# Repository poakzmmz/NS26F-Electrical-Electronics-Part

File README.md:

<p align="center"><sub>Formula Student Korea 2026 2nd Test Week · NS26F</sub></p>

# NS26F Electrical & Electronics

Formula Student 차량의 **전장 시스템과 임베디드 펌웨어를 직접 설계·통합하고 실제 주행 환경에서 검증한 프로젝트**입니다.

회로/PCB 설계뿐 아니라 STM32 기반 데이터 수집 펌웨어, CAN 통신, ADC/DMA, Timer Input Capture, UART 기반 GNSS·IMU, FATFS Logging, Dashboard/Shift Light까지 차량 내 데이터 흐름 전체를 구현했습니다.

> **Portfolio Focus:** Automotive Embedded Software / Vehicle Electronics / MCU Firmware / System Integration

## Project Overview

| 항목 | 내용 |
|---|---|
| Project | NS26F Formula Student Electrical & Electronics System |
| Role | 전장 파트장 |
| Main Scope | Embedded Firmware, Vehicle CAN, Data Logger, PCB, Harness, System Integration |
| MCU | STM32F405RGT6 |
| Interfaces | CAN, ADC, UART, Timer Input Capture, SDIO |
| Software | C, STM32 HAL, DMA/Interrupt, Ring Buffer/Queue, FATFS |
| Tools | STM32CubeIDE, STM32CubeMX, KiCad |
| Validation | 약 200 km 누적 테스트 주행 및 대회 환경 검증 |

## Problem & Goal

전년도 차량은 각 파트가 설계한 성능을 실제 주행 데이터로 정량적으로 확인하기 어려웠습니다.

이를 개선하기 위해 **CAN, Analog Sensor, Wheel Speed, GNSS/IMU처럼 서로 다른 인터페이스의 데이터를 하나의 MCU에서 수집하고 공통 시간축으로 저장하는 차량용 Data Logger**를 개발했습니다.

단순 Logging 장치가 아니라 실제 차량에서 통신·센서 입력·운전자 표시·데이터 저장이 동시에 수행되는 Embedded System을 목표로 했습니다.

## My Contribution

전장 파트장으로 차량 전장 시스템의 설계·제작·통합 및 검증을 총괄했습니다.

### Embedded Software

- STM32F405 기반 Data Logger Firmware 설계 및 구현
- CAN 500 kbps 수신 인터럽트, Frame Queue 및 차량 Signal 처리
- ADC DMA 기반 Analog Sensor Sampling
- Timer Input Capture 기반 Wheel Speed 측정
- UART 기반 GNSS NMEA Parsing 및 IMU DMA 수신/Packet Parsing
- 공통 Timestamp 기반 CAN / ADC / Wheel / IMU Data Aggregation
- microSD + FATFS 기반 CSV Logging
- Blocking SD I/O에 의한 Data Loss를 줄이기 위한 Queue/Ring Buffer 구조 적용
- SD Write Retry, Fault Logging 및 통신 오류 Recovery 로직 구현
- Nextion Dashboard 및 WS2812B Shift Light 출력
- Firmware 기능별 Module Refactoring 및 Legacy/Test Code 정리

### Hardware & System Integration

- STM32 기반 Data Logger 회로 및 PCB 설계
- 차량 CAN Network 및 Sensor Interface 구성
- 전장 Harness 경로 및 배선 구성
- PCB Bring-up / Debugging / 차량 탑재
- Bench Test 및 반복 실차 주행을 통한 시스템 검증

> 이 저장소에는 전장 파트 팀 산출물도 함께 포함되어 있습니다. 위 항목은 개인 포트폴리오 관점에서 직접 수행하거나 주도한 범위를 별도로 정리한 것입니다.

## Embedded Software Architecture

```mermaid
flowchart LR
    CAN[Vehicle CAN] --> CIRQ[CAN RX / Queue]
    ADC[Analog Sensors] --> ADCDMA[ADC DMA]
    WHEEL[Wheel Speed] --> TIM[Timer Input Capture]
    GNSS[GNSS] --> UART1[UART / Ring Buffer]
    IMU[IMU] --> UART6[UART DMA]

    CIRQ --> AGG[Timestamp / Telemetry Aggregation]
    ADCDMA --> AGG
    TIM --> AGG
    UART1 --> AGG
    UART6 --> AGG

    AGG --> LOG[SD Logger / FATFS]
    AGG --> HMI[Nextion Dashboard]
    AGG --> SHIFT[WS2812B Shift Light]
```

### Runtime Design

실차에서는 통신과 센서 입력이 동시에 발생하고 SD Card Write가 수 ms 이상 Blocking될 수 있습니다.

따라서 ISR에서는 가능한 짧게 데이터를 Queue/Ring Buffer에 적재하고, Parsing·Aggregation·File I/O는 foreground loop에서 처리하도록 구성했습니다.

이 구조를 통해 다음 문제를 다뤘습니다.

- CAN/UART 수신 중 SD Write에 의한 입력 손실
- 서로 다른 Sampling Rate의 Sensor Data 동기화
- UART DMA 및 Interrupt Error Recovery
- SD Card Write/Sync 실패 및 Fault 상태 기록
- HMI 출력과 Logging 작업 간 실행시간 간섭

## Requirements → Implementation

초기 요구사항에는 4-bit SDIO와 USB Mass Storage 기능도 포함되어 있었습니다.

실차 검증 과정에서는 **Logging 안정성을 우선하여 SDIO를 1-bit로 운용하고, FATFS가 SD Card를 사용하는 동안 Host와 동시에 접근할 수 있는 USB MSC 기능은 비활성화**했습니다.

즉 초기 명세를 그대로 유지하기보다 실제 차량 환경에서 발생하는 안정성 문제를 기준으로 설계를 조정했습니다.

초기 요구사항과 실제 구현 중 변경된 설계 판단은 [Software Requirements & Design Decisions](dashboard/datalogger/firmware/REQUIREMENTS.md)에 정리했습니다.

## Firmware Structure

현재 공개 Firmware는 약 4,700줄 규모의 단일 `main.c` 구조에서 기능별 Module로 정리했습니다.

```text
Core/
├── Inc/
│   └── app_internal.h
└── Src/
    ├── main.c
    ├── app.c
    ├── app_state.c
    ├── can_bus.c
    ├── adc_input.c
    ├── wheel_speed.c
    ├── gnss.c
    ├── imu.c
    ├── telemetry.c
    ├── sd_logger.c
    ├── dashboard.c
    ├── shiftlight.c
    ├── app_callbacks.c
    └── led_diag.c
```

각 기능의 책임과 상세 구현은 [Datalogger Firmware](dashboard/datalogger/firmware/README.md)에서 확인할 수 있습니다.

> 실제 차량에서 사용된 통합 Firmware의 동작 경험을 바탕으로 공개 코드 구조를 Module 단위로 정리했습니다. 현재 Refactor Code는 정적 구조 검사를 완료했으며, Hardware Regression은 별도 환경에서 재확인이 필요합니다.

## Hardware & Vehicle Validation

<table>
<tr>
<td width="50%" align="center">
<br>
<sub>STM32 기반 Data Logger PCB — 직접 설계·제작한 V1 보드</sub>
</td>
<td width="50%" align="center">
<br>
<sub>차량 탑재 전/개발 중 전장 Integration Test</sub>
</td>
</tr>
<tr>
<td width="50%" align="center">
<br>
<sub>Dashboard 내부 실제 차량 장착 및 전장 통합</sub>
</td>
<td width="50%" align="center">
<br>
<sub>차량 Harness 제작 및 배선 통합</sub>
</td>
</tr>
</table>

> Integration Test 사진은 개발/검증 단계의 임시 배선을 포함합니다. 최종 양산 배선 품질을 나타내기 위한 사진이 아니라 실제 차량에서 Interface와 기능을 확인한 개발 과정 기록입니다.

## Verification

1. Interface 단위 기능 확인
2. CAN / ADC / Timer / UART 개별 입력 검증
3. SD Logging 및 파일 무결성 확인
4. Dashboard / Shift Light 출력 통합
5. 차량 탑재 후 Sensor / ECU / Harness 통합
6. 반복 주행 중 Data Loss 및 통신 오류 확인
7. 문제 수정 후 재검증

완성된 전장 시스템과 Data Logger는 약 200 km의 누적 테스트 주행과 Formula Student 대회 환경에서 사용했습니다.

> 본 프로젝트의 검증 범위는 Formula Student 차량의 개발 및 대회 환경입니다. 양산 자동차 규격(AEC-Q, ISO 16750 등)에 따른 Automotive Qualification을 의미하지 않습니다.

## Other Electrical Modules

| Module | Description | Path |
|---|---|---|
| Brake Light | LED Brake Light PCB, KiCad 및 생산 파일 | [`brake-light/`](brake-light/) |
| Data Logger | STM32 기반 다채널 차량 Data Acquisition System | [`dashboard/datalogger/`](dashboard/datalogger/) |
| Dashboard UI | Nextion 기반 운전자 표시 UI | [`dashboard/display-ui/`](dashboard/display-ui/) |
| Shift Light | WS2812B 기반 RPM Shift Light | [`dashboard/shiftlight/`](dashboard/shiftlight/) |
| Telemetry | LoRa 기반 차량 데이터 무선 전송 및 Viewer | [`telemetry/`](telemetry/) |
| Harness | 차량 전장 Harness 자료 | [`harness/`](harness/) |

## Repository Structure

```text
NS26F-Electrical-Electronics-Part/
├── brake-light/
├── dashboard/
│   ├── display-ui/
│   ├── datalogger/
│   │   ├── hardware/
│   │   └── firmware/
│   └── shiftlight/
├── telemetry/
├── harness/
└── docs/
```

## Documents

- [Data Logger](dashboard/datalogger/README.md)
- [Data Logger Hardware](dashboard/datalogger/hardware/README.md)
- [Data Logger Firmware](dashboard/datalogger/firmware/README.md)
- [Brake Light](brake-light/README.md)
- [Shift Light](dashboard/shiftlight/README.md)
- [Telemetry](telemetry/README.md)

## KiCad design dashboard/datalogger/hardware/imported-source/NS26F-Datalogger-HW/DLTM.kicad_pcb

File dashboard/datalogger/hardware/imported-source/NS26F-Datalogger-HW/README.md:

# NS26F Datalogger HW

NS26F 데이터로거 KiCad 프로젝트.

## 하드웨어

- MCU: STM32F405RGT6
- 외부 크리스털: 8 MHz
- 3.3 V 레귤레이터: AMS1117-3.3
- CAN 트랜시버: SN65HVD230
- microSD: SDIO 4-bit
- USB Type-C
- SWD
- ADC 입력 6채널
- Input Capture 4채널
- 상태 LED 2채널

## 파일

- `DLTM.kicad_sch`: 회로도
- `DLTM.kicad_pcb`: PCB
- `DLTM.kicad_pro`: 프로젝트 설정
- `DLTM.pdf`: 회로도 PDF
- `production/`: BOM, 실장 좌표, 생산 파일

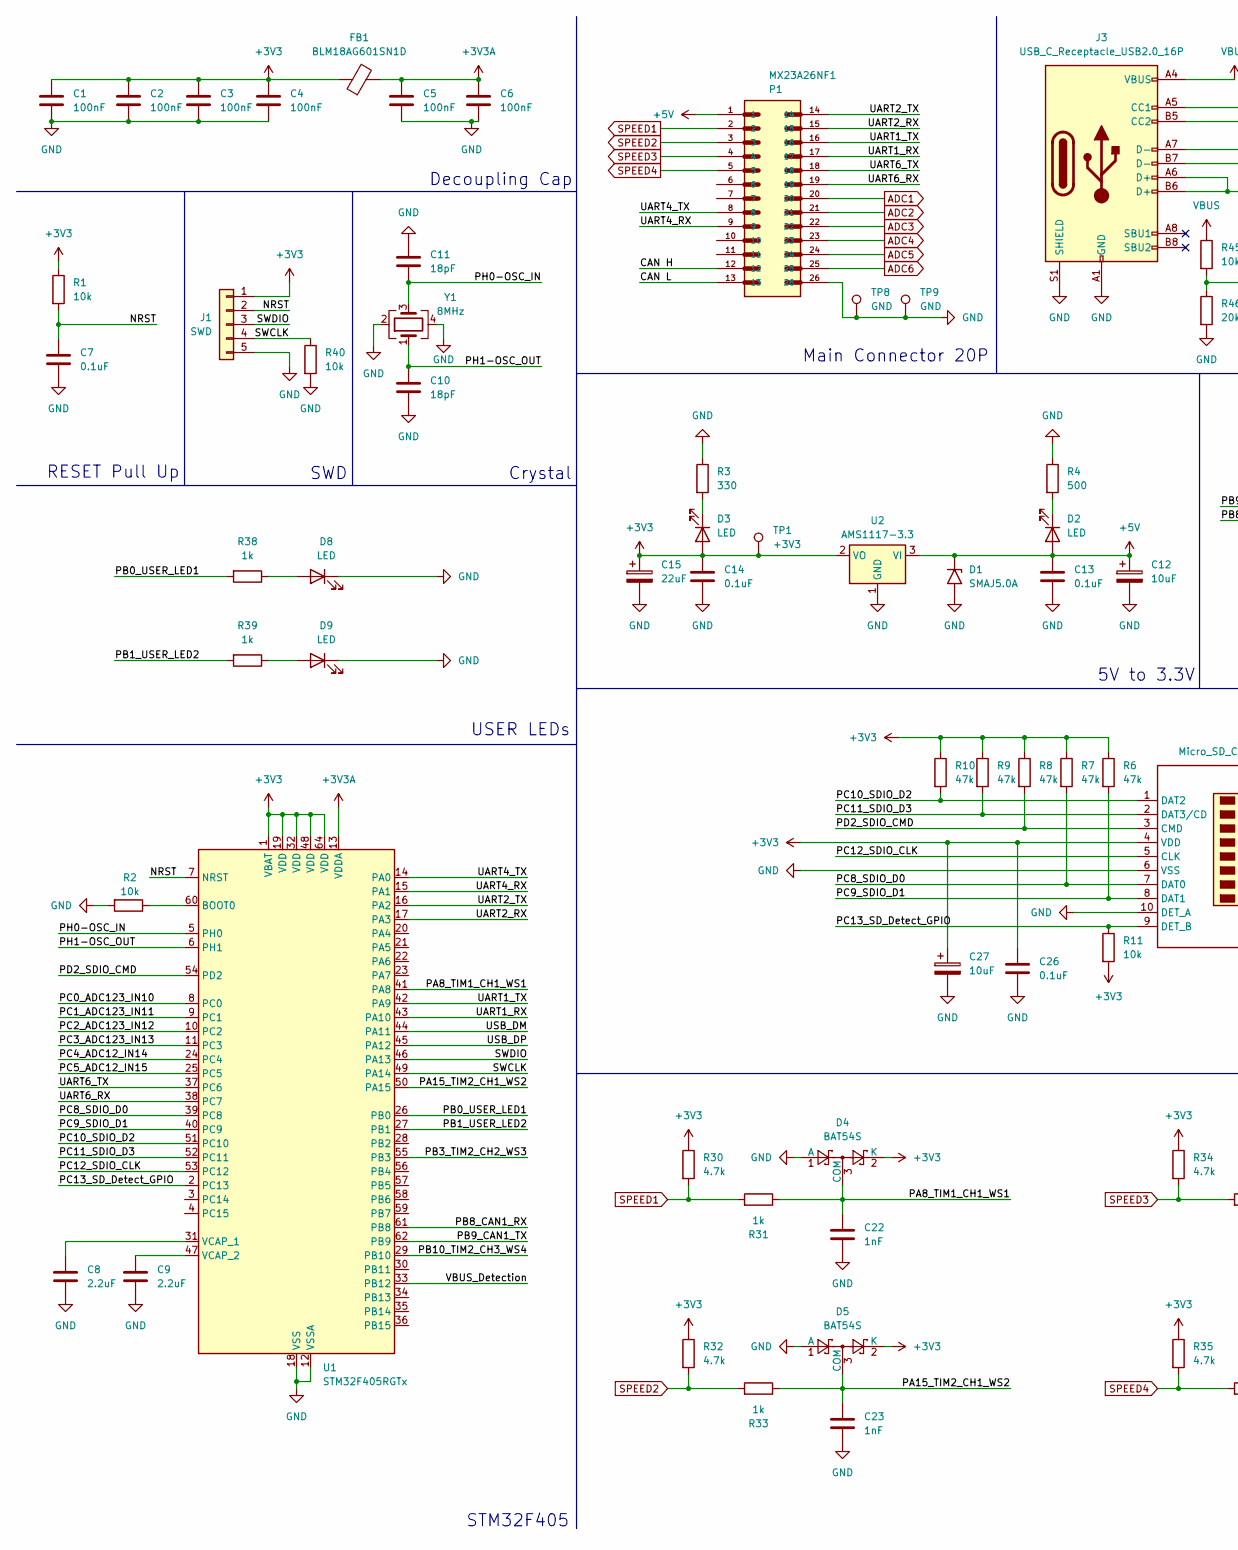
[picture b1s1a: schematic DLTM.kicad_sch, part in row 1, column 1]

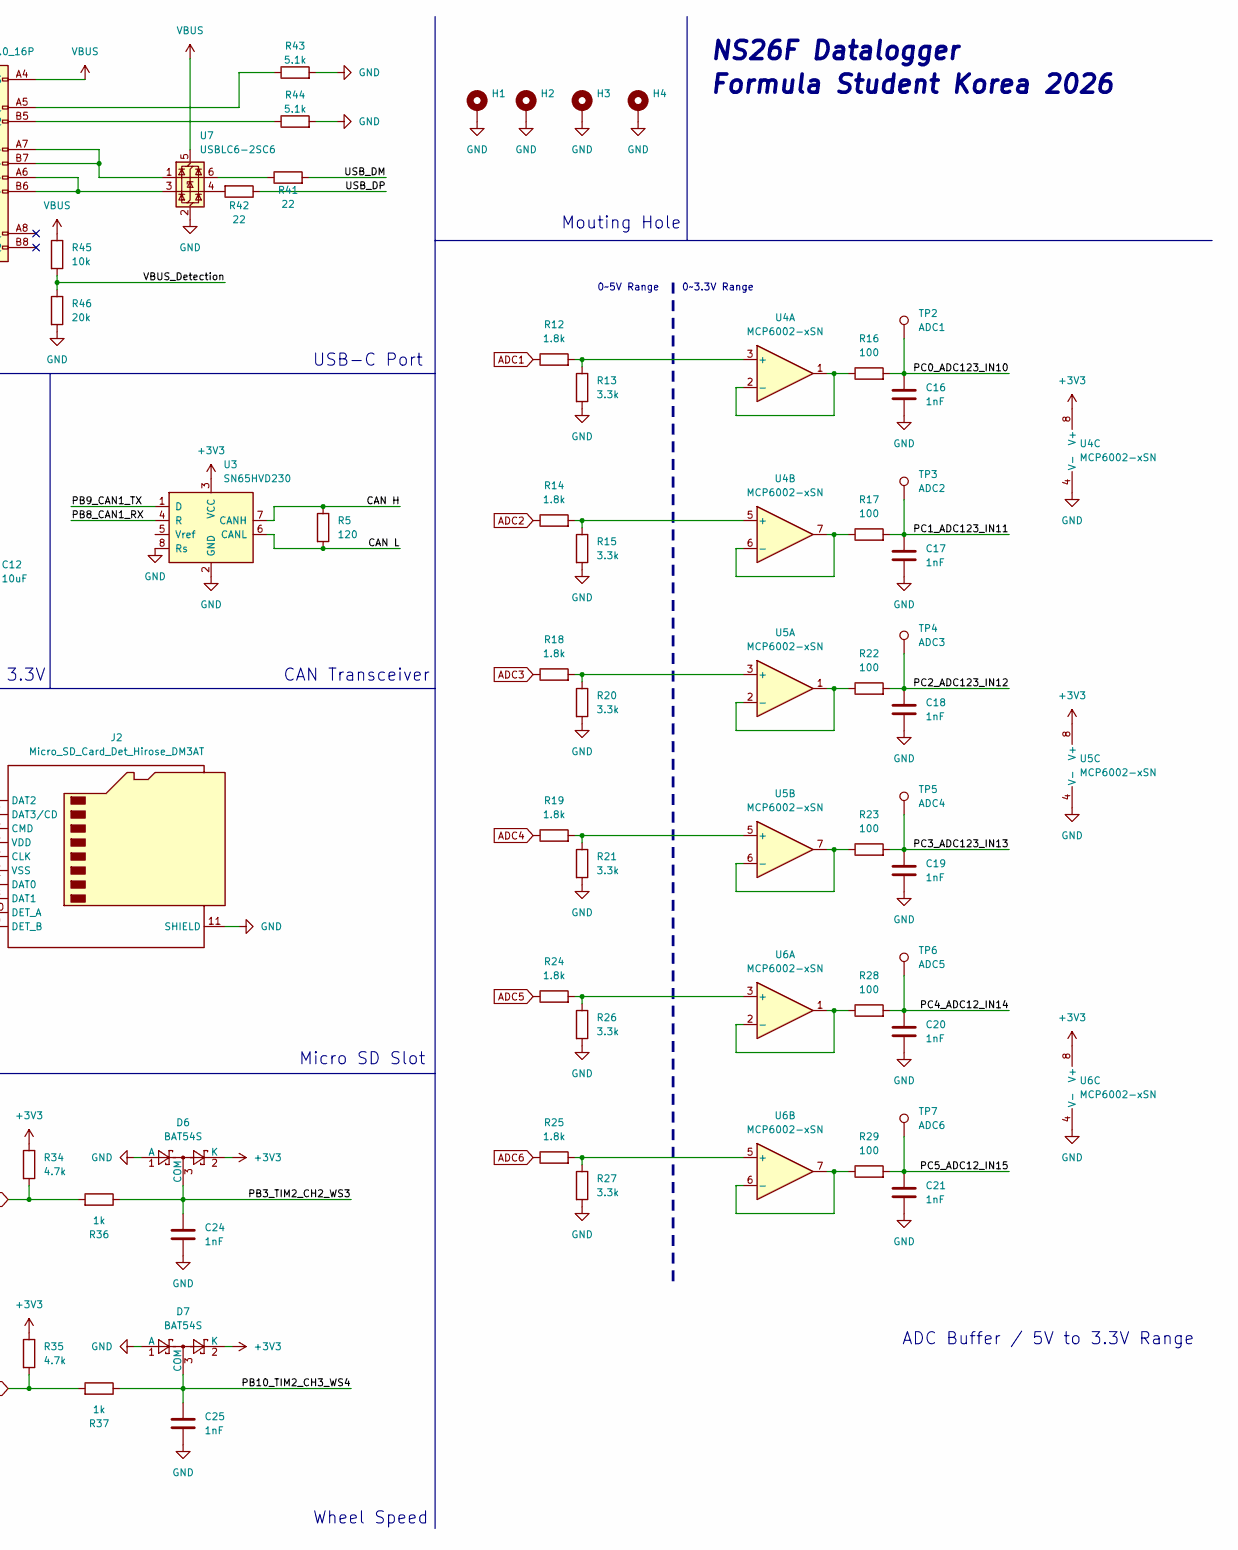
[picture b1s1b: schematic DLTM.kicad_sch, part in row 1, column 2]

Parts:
C1, C2, C3, C4, C5, C6: 100nF; C_0603_1608Metric
C7, C13, C14, C26: 0.1uF; C_0603_1608Metric
C8, C9: 2.2uF; C_0603_1608Metric
C10, C11: 18pF; C_0603_1608Metric
C12, C27: 10uF; CP_Elec_4x5.4
C15: 22uF; CP_Elec_4x5.4
C16, C17, C18, C19, C20, C21, C22, C23, C24, C25: 1nF; C_0603_1608Metric
D1: SMAJ5.0A; D_SMA
D2, D3, D8, D9: LED; LED_0603_1608Metric
D4, D5, D6, D7: BAT54S; SOT-23
FB1: BLM18AG601SN1D; L_0603_1608Metric
H1, H2, H3, H4: MountingHole_Pad; MountingHole_3mm_Pad_TopBottom
J1: SWD; PinHeader_1x05_P2.54mm_Vertical
J2: Micro_SD_Card_Det_Hirose_DM3AT; microSD_HC_Hirose_DM3AT-SF-PEJM5
J3: USB_C_Receptacle_USB2.0_16P; USB_C_Receptacle_HRO_TYPE-C-31-M-12
P1: MX23A26NF1; JAE_MX23A26NF1
R1, R2, R11, R40, R45: 10k; R_0603_1608Metric
R3: 330; R_0603_1608Metric
R4: 500; R_0603_1608Metric
R5: 120; R_0603_1608Metric
R6, R7, R8, R9, R10: 47k; R_0603_1608Metric
R12, R14, R18, R19, R24, R25: 1.8k; R_0603_1608Metric
R13, R15, R20, R21, R26, R27: 3.3k; R_0603_1608Metric
R16, R17, R22, R23, R28, R29: 100; R_0603_1608Metric
R30, R32, R34, R35: 4.7k; R_0603_1608Metric
R31, R33, R36, R37, R38, R39: 1k; R_0603_1608Metric
R41, R42: 22; R_0603_1608Metric
R43, R44: 5.1k; R_0603_1608Metric
R46: 20k; R_0603_1608Metric
TP1: +3V3; TestPoint_Loop_D1.80mm_Drill1.0mm_Beaded
TP2: ADC1; TestPoint_Pad_1.0x1.0mm
TP3: ADC2; TestPoint_Pad_1.0x1.0mm
TP4: ADC3; TestPoint_Pad_1.0x1.0mm
TP5: ADC4; TestPoint_Pad_1.0x1.0mm
TP6: ADC5; TestPoint_Pad_1.0x1.0mm
TP7: ADC6; TestPoint_Pad_1.0x1.0mm
TP8, TP9: GND; TestPoint_Loop_D1.80mm_Drill1.0mm_Beaded
U1: STM32F405RGTx; LQFP-64_10x10mm_P0.5mm
U2: AMS1117-3.3; SOT-223-3_TabPin2
U3: SN65HVD230; SOIC-8_3.9x4.9mm_P1.27mm
U4, U5, U6: MCP6002-xSN; SOIC-8_3.9x4.9mm_P1.27mm
U7: USBLC6-2SC6; SOT-23-6
Y1: 8MHz; Crystal_SMD_3225-4Pin_3.2x2.5mm

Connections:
+3V3: C1.1, C2.1, C3.1, C4.1, C14.1, C15.1, C26.1, C27.1, D3.2 (A), D4.2 (K), D5.2 (K), D6.2 (K), D7.2 (K), FB1.1, J1.1, J2.4 (VDD), R1.1, R6.1, R7.1, R8.1, R9.1, R10.1, R11.2, R30.1, R32.1, R34.1, R35.1, TP1.1, U1.1 (VBAT), U1.19 (VDD), U1.32 (VDD), U1.48 (VDD), U1.64 (VDD), U2.2 (VO), U3.3 (VCC), U4.8 (V+), U5.8 (V+), U6.8 (V+)
+3V3A: C5.1, C6.1, FB1.2, U1.13 (VDDA)
+5V: C12.1, C13.1, D1.1 (A1), D2.2 (A), P1.1, U2.3 (VI)
/CAN H: P1.12, R5.1, U3.7 (CANH)
/CAN L: P1.13, R5.2, U3.6 (CANL)
/NRST: C7.1, J1.2, R1.2, U1.7 (NRST)
/PA8_TIM1_CH1_WS1: C22.1, D4.3 (COM), R31.1, U1.41 (PA8)
/PA15_TIM2_CH1_WS2: C23.1, D5.3 (COM), R33.1, U1.50 (PA15)
/PB0_USER_LED1: R38.2, U1.26 (PB0)
/PB1_USER_LED2: R39.2, U1.27 (PB1)
/PB3_TIM2_CH2_WS3: C24.1, D6.3 (COM), R36.1, U1.55 (PB3)
/PB8_CAN1_RX: U1.61 (PB8), U3.4 (R)
/PB9_CAN1_TX: U1.62 (PB9), U3.1 (D)
/PB10_TIM2_CH3_WS4: C25.1, D7.3 (COM), R37.1, U1.29 (PB10)
/PC0_ADC123_IN10: C16.1, R16.2, TP2.1, U1.8 (PC0)
/PC1_ADC123_IN11: C17.1, R17.2, TP3.1, U1.9 (PC1)
/PC2_ADC123_IN12: C18.1, R22.2, TP4.1, U1.10 (PC2)
/PC3_ADC123_IN13: C19.1, R23.2, TP5.1, U1.11 (PC3)
/PC4_ADC12_IN14: C20.1, R28.2, TP6.1, U1.24 (PC4)
/PC5_ADC12_IN15: C21.1, R29.2, TP7.1, U1.25 (PC5)
/PC8_SDIO_D0: J2.7 (DAT0), R7.2, U1.39 (PC8)
/PC9_SDIO_D1: J2.8 (DAT1), R6.2, U1.40 (PC9)
/PC10_SDIO_D2: J2.1 (DAT2), R10.2, U1.51 (PC10)
/PC11_SDIO_D3: J2.2 (DAT3/CD), R9.2, U1.52 (PC11)
/PC12_SDIO_CLK: J2.5 (CLK), U1.53 (PC12)
/PC13_SD_Detect_GPIO: J2.9 (DET_B), R11.1, U1.2 (PC13)
/PD2_SDIO_CMD: J2.3 (CMD), R8.2, U1.54 (PD2)
/PH0-OSC_IN: C11.2, U1.5 (PH0), Y1.3
/PH1-OSC_OUT: C10.1, U1.6 (PH1), Y1.1
/SWCLK: J1.4, R40.1, U1.49 (PA14)
/SWDIO: J1.3, U1.46 (PA13)
/UART1_RX: P1.17, U1.43 (PA10)
/UART1_TX: P1.16, U1.42 (PA9)
/UART2_RX: P1.15, U1.17 (PA3)
/UART2_TX: P1.14, U1.16 (PA2)
/UART4_RX: P1.9, U1.15 (PA1)
/UART4_TX: P1.8, U1.14 (PA0)
/UART6_RX: P1.19, U1.38 (PC7)
/UART6_TX: P1.18, U1.37 (PC6)
/USB_DM: R41.2, U1.44 (PA11)
/USB_DP: R42.1, U1.45 (PA12)
/VBUS_Detection: R45.2, R46.1, U1.33 (PB12)
ADC1: P1.20, R12.1
ADC2: P1.21, R14.1
ADC3: P1.22, R18.1
ADC4: P1.23, R19.1
ADC5: P1.24, R24.1
ADC6: P1.25, R25.1
GND: C1.2, C2.2, C3.2, C4.2, C5.2, C6.2, C7.2, C8.2, C9.2, C10.2, C11.1, C12.2, C13.2, C14.2, C15.2, C16.2, C17.2, C18.2, C19.2, C20.2, C21.2, C22.2, C23.2, C24.2, C25.2, C26.2, C27.2, D1.2 (A2), D4.1 (A), D5.1 (A), D6.1 (A), D7.1 (A), D8.1 (K), D9.1 (K), H1.1, H2.1, H3.1, H4.1, J1.5, J2.6 (VSS), J2.10 (DET_A), J2.11 (SHIELD), J3.A1 (GND), J3.A12 (GND), J3.B1 (GND), J3.B12 (GND), J3.S1 (SHIELD), P1.26, R2.2, R3.1, R4.1, R13.2, R15.2, R20.2, R21.2, R26.2, R27.2, R40.2, R43.2, R44.2, R46.2, TP8.1, TP9.1, U1.12 (VSSA), U1.18 (VSS), U1.63 (VSS), U2.1 (GND), U3.2 (GND), U3.8 (Rs), U4.4 (V-), U5.4 (V-), U6.4 (V-), U7.2 (GND), Y1.2, Y1.4
unnamed: D2.1 (K), R4.2
unnamed: D3.1 (K), R3.2
unnamed: D8.2 (A), R38.1
unnamed: D9.2 (A), R39.1
unnamed: J3.A5 (CC1), R43.1
unnamed: J3.B5 (CC2), R44.1
unnamed: J3.A6 (D+), J3.B6 (D+), U7.3 (I/O2)
unnamed: J3.A7 (D-), J3.B7 (D-), U7.1 (I/O1)
unnamed: R41.1, U7.6 (I/O1)
unnamed: R42.2, U7.4 (I/O2)
unnamed: R2.1, U1.60 (BOOT0)
unnamed: C8.1, U1.31 (VCAP_1)
unnamed: C9.1, U1.47 (VCAP_2)
unnamed: R12.2, R13.1, U4.3 (+)
unnamed: R16.1, U4.1, U4.2 (-)
unnamed: R14.2, R15.1, U4.5 (+)
unnamed: R17.1, U4.6 (-), U4.7
unnamed: R18.2, R20.1, U5.3 (+)
unnamed: R22.1, U5.1, U5.2 (-)
unnamed: R19.2, R21.1, U5.5 (+)
unnamed: R23.1, U5.6 (-), U5.7
unnamed: R24.2, R26.1, U6.3 (+)
unnamed: R28.1, U6.1, U6.2 (-)
unnamed: R25.2, R27.1, U6.5 (+)
unnamed: R29.1, U6.6 (-), U6.7
SPEED1: P1.2, R30.2, R31.2
SPEED2: P1.3, R32.2, R33.2
SPEED3: P1.4, R34.2, R36.2
SPEED4: P1.5, R35.2, R37.2
VBUS: J3.A4 (VBUS), J3.A9 (VBUS), J3.B4 (VBUS), J3.B9 (VBUS), R45.1, U7.5 (VBUS)

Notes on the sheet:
0~3.3V Range
USB-C Port
Main Connector 20P
STM32F405
Decoupling Cap
USER LEDs
Mouting Hole
NS26F Datalogger
Micro SD Slot
CAN Transceiver
Formula Student Korea 2026
RESET Pull Up
Wheel Speed
5V to 3.3V
ADC Buffer / 5V to 3.3V Range
Crystal
SWD
0~5V Range

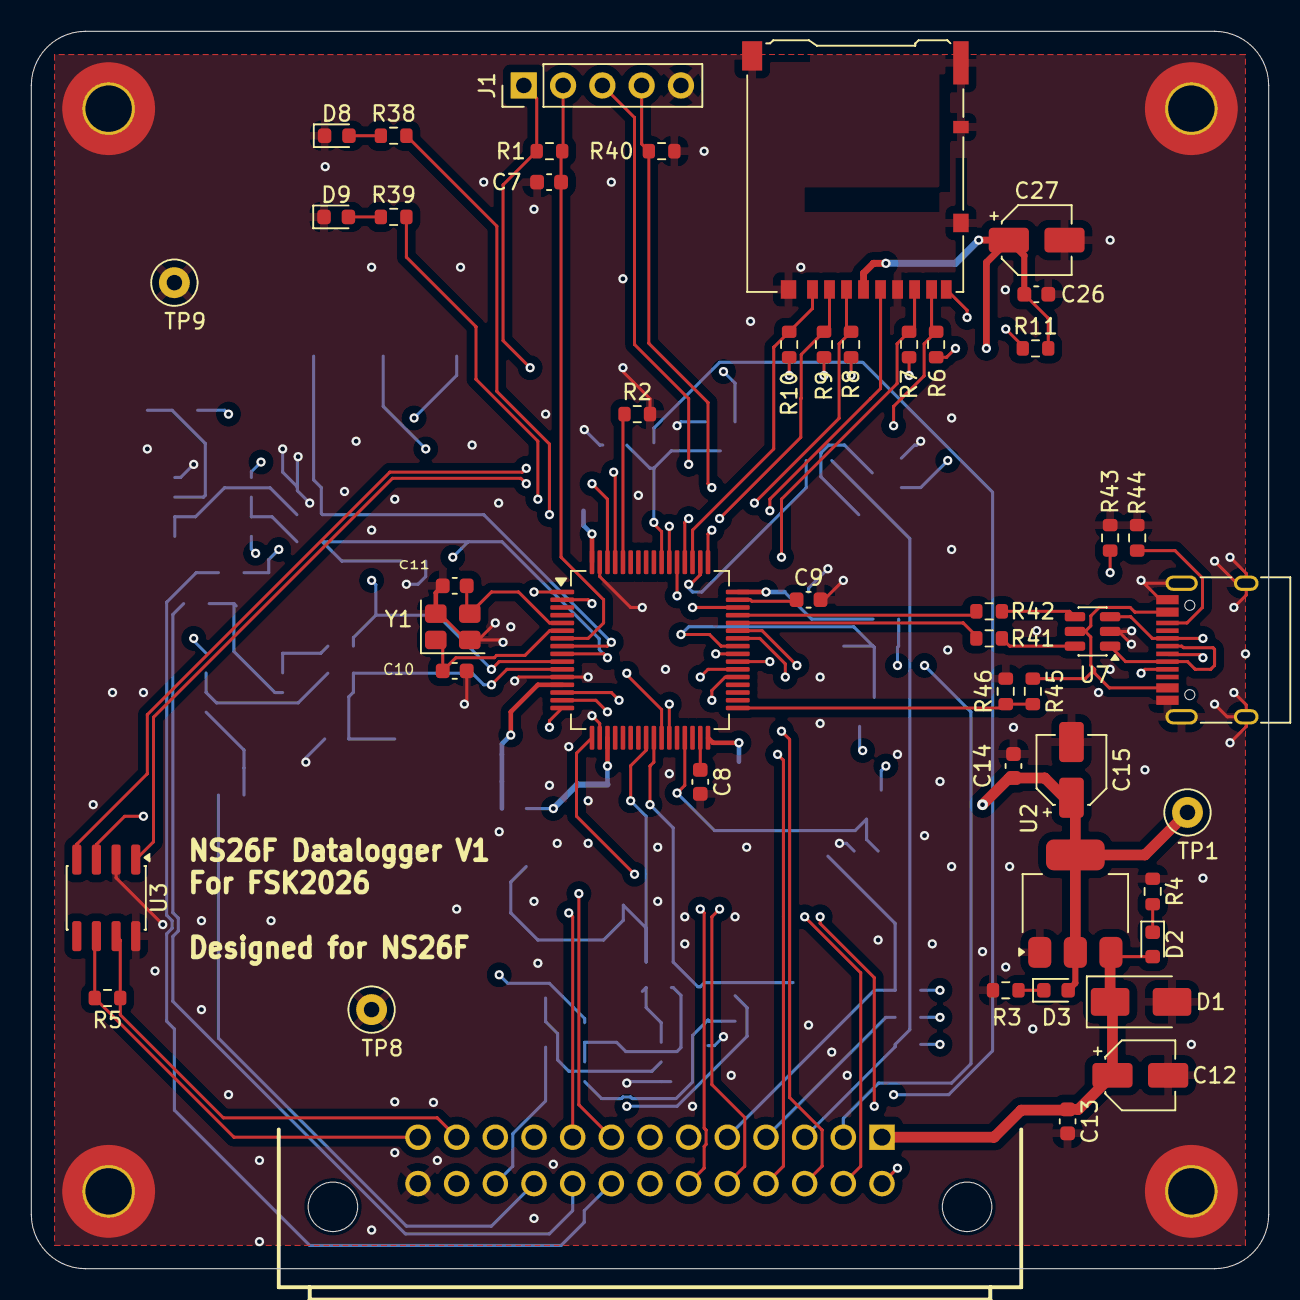
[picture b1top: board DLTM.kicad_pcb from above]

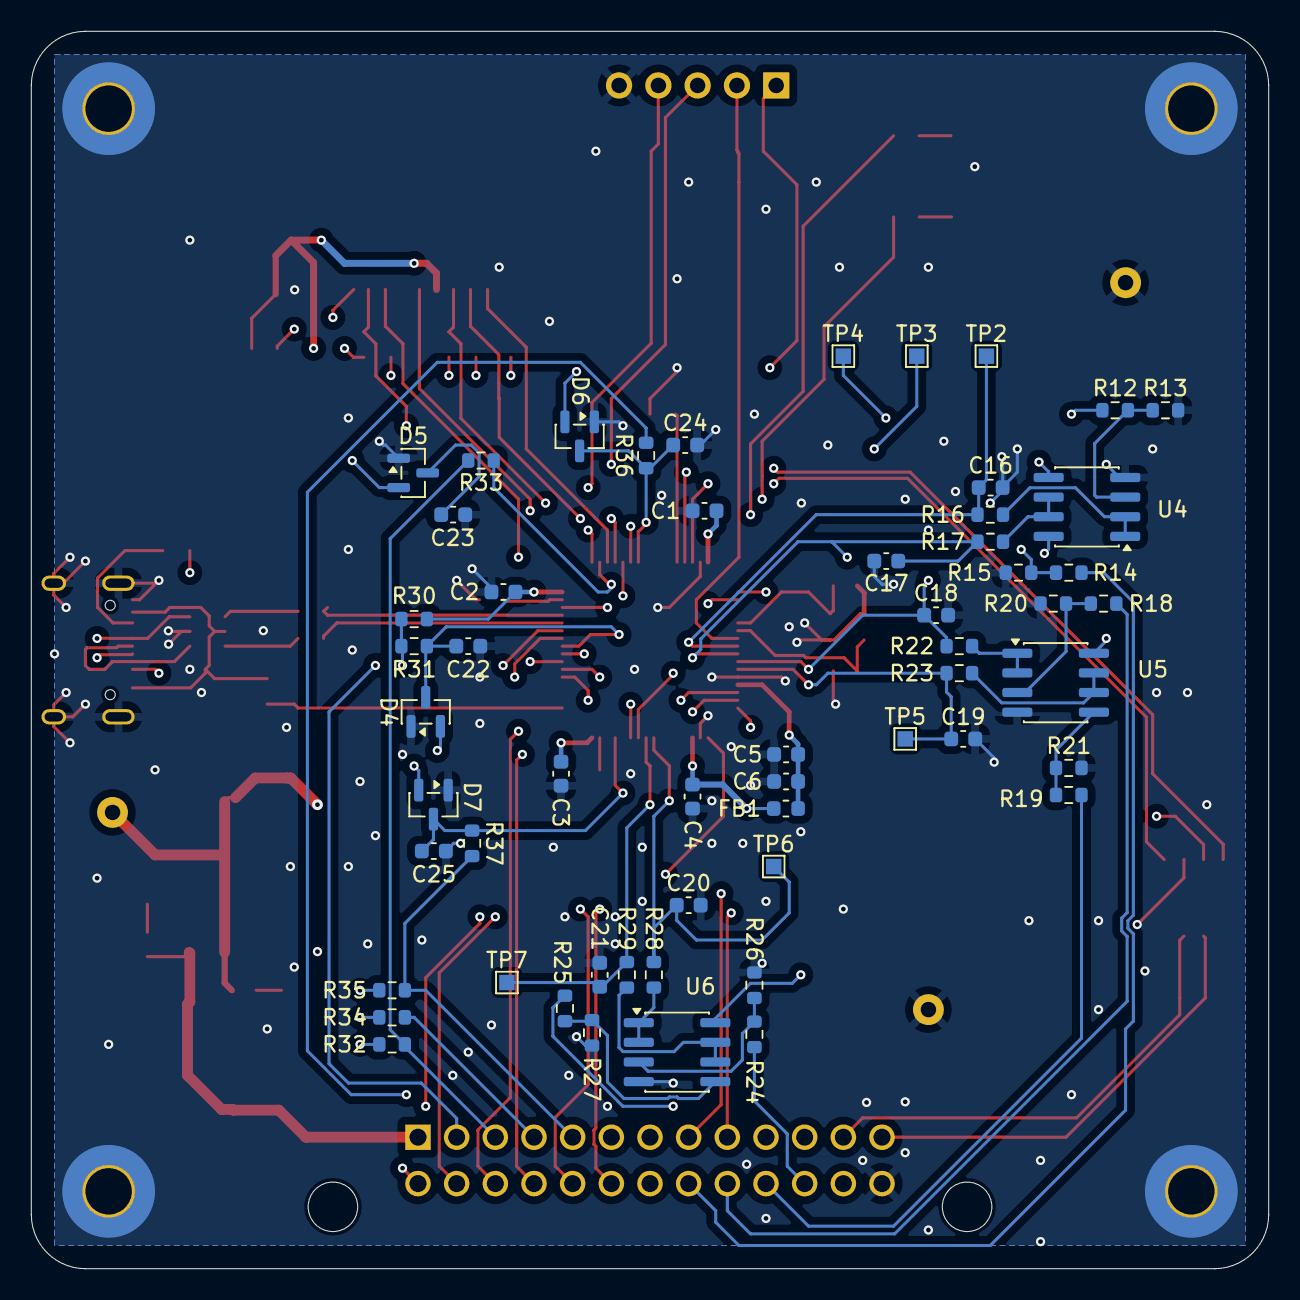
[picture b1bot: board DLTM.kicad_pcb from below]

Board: 4 copper layers, 80.0 x 80.0 mm, 108 parts (56 on the bottom side), 79 nets.

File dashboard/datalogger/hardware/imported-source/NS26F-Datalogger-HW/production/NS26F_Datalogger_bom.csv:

Designator,Footprint,Quantity,Value,LCSC Part #
"C1, C2, C3, C4, C5, C6",0603,6,100nF,
"C10, C11",0603,2,18pF,
"C12, C27",CP_Elec_4x5.4,2,10uF,
"C13, C14, C26, C7",0603,4,0.1uF,
C15,CP_Elec_4x5.4,1,22uF,
"C16, C17, C18, C19, C20, C21, C22, C23, C24, C25",0603,10,1nF,
"C8, C9",0603,2,2.2uF,
D1,D_SMA,1,SMAJ5.0A,
"D2, D3, D8, D9",0603,4,LED,
"D4, D5, D6, D7",SOT-23,4,BAT54S,
FB1,0603,1,BLM18AG601SN1D,
J1,PinHeader_1x05_P2.54mm_Vertical,1,SWD,
J2,microSD_HC_Hirose_DM3AT-SF-PEJM5,1,Micro_SD_Card_Det_Hirose_DM3AT,
J3,USB_C_Receptacle_HRO_TYPE-C-31-M-12,1,USB_C_Receptacle_USB2.0_16P,
P1,JAE_MX23A26NF1,1,MX23A26NF1,
"R1, R11, R2, R40, R45",0603,5,10k,
"R10, R6, R7, R8, R9",0603,5,47k,
"R12, R14, R18, R19, R24, R25",0603,6,1.8k,
"R13, R15, R20, R21, R26, R27",0603,6,3.3k,
"R16, R17, R22, R23, R28, R29",0603,6,100,
R3,0603,1,330,
"R30, R32, R34, R35",0603,4,4.7k,
"R31, R33, R36, R37, R38, R39",0603,6,1k,
R4,0603,1,500,
"R41, R42",0603,2,22,
"R43, R44",0603,2,5.1k,
R46,0603,1,20k,
R5,0603,1,120,
TP1,TestPoint_Loop_D1.80mm_Drill1.0mm_Beaded,1,+3V3,
TP2,TestPoint_Pad_1.0x1.0mm,1,ADC1,
TP3,TestPoint_Pad_1.0x1.0mm,1,ADC2,
TP4,TestPoint_Pad_1.0x1.0mm,1,ADC3,
TP5,TestPoint_Pad_1.0x1.0mm,1,ADC4,
TP6,TestPoint_Pad_1.0x1.0mm,1,ADC5,
TP7,TestPoint_Pad_1.0x1.0mm,1,ADC6,
"TP8, TP9",TestPoint_Loop_D1.80mm_Drill1.0mm_Beaded,2,GND,
U1,LQFP-64_10x10mm_P0.5mm,1,STM32F405RGTx,
U2,SOT-223-3_TabPin2,1,AMS1117-3.3,
U3,SOIC-8_3.9x4.9mm_P1.27mm,1,SN65HVD230,
"U4, U5, U6",SOIC-8_3.9x4.9mm_P1.27mm,3,MCP6002-xSN,
U7,SOT-23-6,1,USBLC6-2SC6,
Y1,Crystal_SMD_3225-4Pin_3.2x2.5mm,1,8MHz,

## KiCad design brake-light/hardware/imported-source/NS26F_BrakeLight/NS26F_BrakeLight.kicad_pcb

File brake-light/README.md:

# NS26F Brake Light

NS26F 브레이크등 KiCad 프로젝트.

## 구성

- 0805 LED 68개
- 330 Ω 1206 저항 17개
- TVS 다이오드 1개
- SS34 다이오드 1개

## 파일

- `hardware/imported-source/NS26F_BrakeLight/NS26F_BrakeLight.kicad_sch`: 회로도
- `hardware/imported-source/NS26F_BrakeLight/NS26F_BrakeLight.kicad_pcb`: PCB
- `hardware/imported-source/NS26F_BrakeLight/production/`: BOM, 실장 좌표, 생산 ZIP

`production/`에는 초기 버전과 V2 파일이 함께 있다. 두 버전의 BOM 내용은 같다.

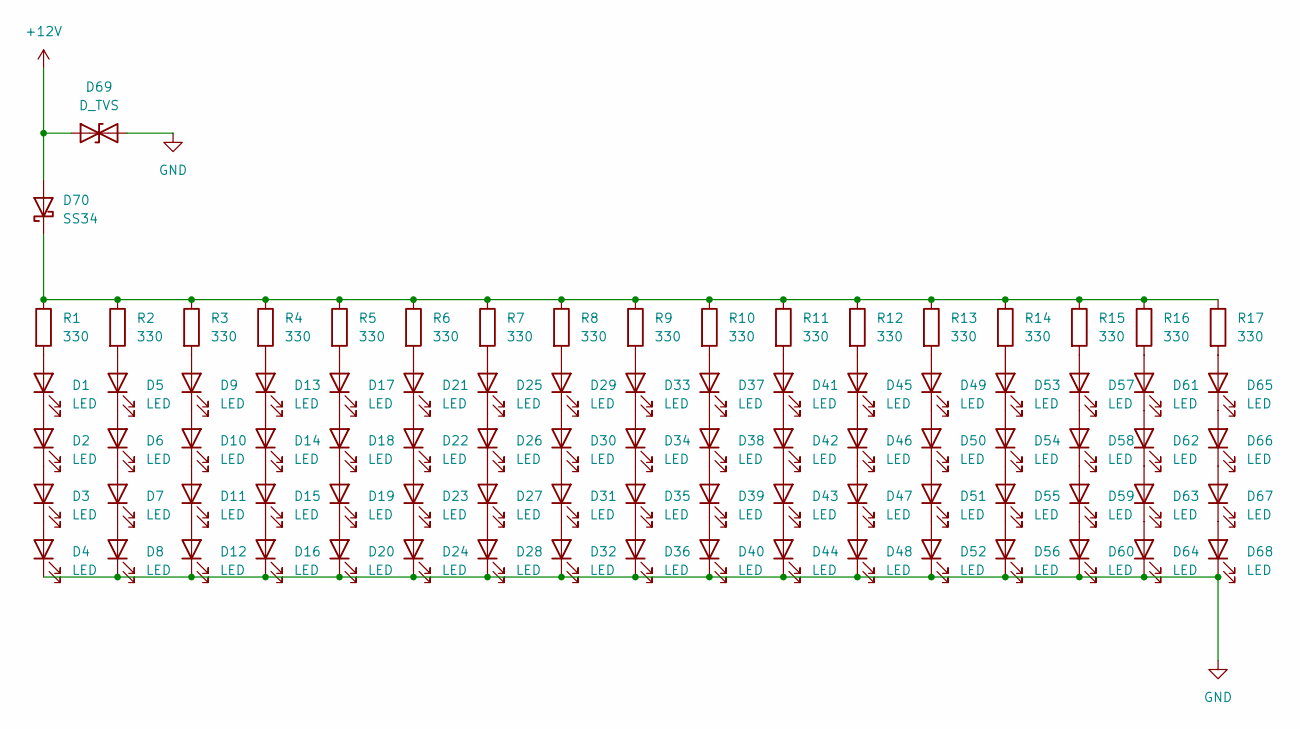
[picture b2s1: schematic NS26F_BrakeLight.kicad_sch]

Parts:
D1, D2, D3, D4, D5, D6, D7, D8, D9, D10, D11, D12, D13, D14, D15, D16, D17, D18, D19, D20, D21, D22, D23, D24, D25, D26, D27, D28, D29, D30, D31, D32, D33, D34, D35, D36, D37, D38, D39, D40, D41, D42, D43, D44, D45, D46, D47, D48, D49, D50, D51, D52, D53, D54, D55, D56, D57, D58, D59, D60, D61, D62, D63, D64, D65, D66, D67, D68: LED; LED_0805_2012Metric_Pad1.15x1.40mm_HandSolder
D69: D_TVS; D_SMC
D70: SS34; D_SMA
R1, R2, R3, R4, R5, R6, R7, R8, R9, R10, R11, R12, R13, R14, R15, R16, R17: 330; R_1206_3216Metric_Pad1.30x1.75mm_HandSolder

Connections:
+12V: D69.1 (A1), D70.2 (A); also elsewhere on the board
GND: D4.1 (K), D8.1 (K), D12.1 (K), D16.1 (K), D20.1 (K), D24.1 (K), D28.1 (K), D32.1 (K), D36.1 (K), D40.1 (K), D44.1 (K), D48.1 (K), D52.1 (K), D56.1 (K), D60.1 (K), D64.1 (K), D68.1 (K), D69.2 (A2); also elsewhere on the board
unnamed: D1.2 (A), R1.2
unnamed: D1.1 (K), D2.2 (A)
unnamed: D2.1 (K), D3.2 (A)
unnamed: D3.1 (K), D4.2 (A)
unnamed: D5.2 (A), R2.2
unnamed: D5.1 (K), D6.2 (A)
unnamed: D6.1 (K), D7.2 (A)
unnamed: D7.1 (K), D8.2 (A)
unnamed: D9.2 (A), R3.2
unnamed: D9.1 (K), D10.2 (A)
unnamed: D10.1 (K), D11.2 (A)
unnamed: D11.1 (K), D12.2 (A)
unnamed: D13.2 (A), R4.2
unnamed: D13.1 (K), D14.2 (A)
unnamed: D14.1 (K), D15.2 (A)
unnamed: D15.1 (K), D16.2 (A)
unnamed: D17.2 (A), R5.2
unnamed: D17.1 (K), D18.2 (A)
unnamed: D18.1 (K), D19.2 (A)
unnamed: D19.1 (K), D20.2 (A)
unnamed: D21.2 (A), R6.2
unnamed: D21.1 (K), D22.2 (A)
unnamed: D22.1 (K), D23.2 (A)
unnamed: D23.1 (K), D24.2 (A)
unnamed: D25.2 (A), R7.2
unnamed: D25.1 (K), D26.2 (A)
unnamed: D26.1 (K), D27.2 (A)
unnamed: D27.1 (K), D28.2 (A)
unnamed: D29.2 (A), R8.2
unnamed: D29.1 (K), D30.2 (A)
unnamed: D30.1 (K), D31.2 (A)
unnamed: D31.1 (K), D32.2 (A)
unnamed: D33.2 (A), R9.2
unnamed: D33.1 (K), D34.2 (A)
unnamed: D34.1 (K), D35.2 (A)
unnamed: D35.1 (K), D36.2 (A)
unnamed: D37.2 (A), R10.2
unnamed: D37.1 (K), D38.2 (A)
unnamed: D38.1 (K), D39.2 (A)
unnamed: D39.1 (K), D40.2 (A)
unnamed: D41.2 (A), R11.2
unnamed: D41.1 (K), D42.2 (A)
unnamed: D42.1 (K), D43.2 (A)
unnamed: D43.1 (K), D44.2 (A)
unnamed: D45.2 (A), R12.2
unnamed: D45.1 (K), D46.2 (A)
unnamed: D46.1 (K), D47.2 (A)
unnamed: D47.1 (K), D48.2 (A)
unnamed: D49.2 (A), R13.2
unnamed: D49.1 (K), D50.2 (A)
unnamed: D50.1 (K), D51.2 (A)
unnamed: D51.1 (K), D52.2 (A)
unnamed: D53.2 (A), R14.2
unnamed: D53.1 (K), D54.2 (A)
unnamed: D54.1 (K), D55.2 (A)
unnamed: D55.1 (K), D56.2 (A)
unnamed: D57.2 (A), R15.2
unnamed: D57.1 (K), D58.2 (A)
unnamed: D58.1 (K), D59.2 (A)
unnamed: D59.1 (K), D60.2 (A)
unnamed: D61.2 (A), R16.2
unnamed: D61.1 (K), D62.2 (A)
unnamed: D62.1 (K), D63.2 (A)
unnamed: D63.1 (K), D64.2 (A)
unnamed: D65.2 (A), R17.2
unnamed: D65.1 (K), D66.2 (A)
unnamed: D66.1 (K), D67.2 (A)
unnamed: D67.1 (K), D68.2 (A)
unnamed: D70.1 (K), R1.1, R2.1, R3.1, R4.1, R5.1, R6.1, R7.1, R8.1, R9.1, R10.1, R11.1, R12.1, R13.1, R14.1, R15.1, R16.1, R17.1

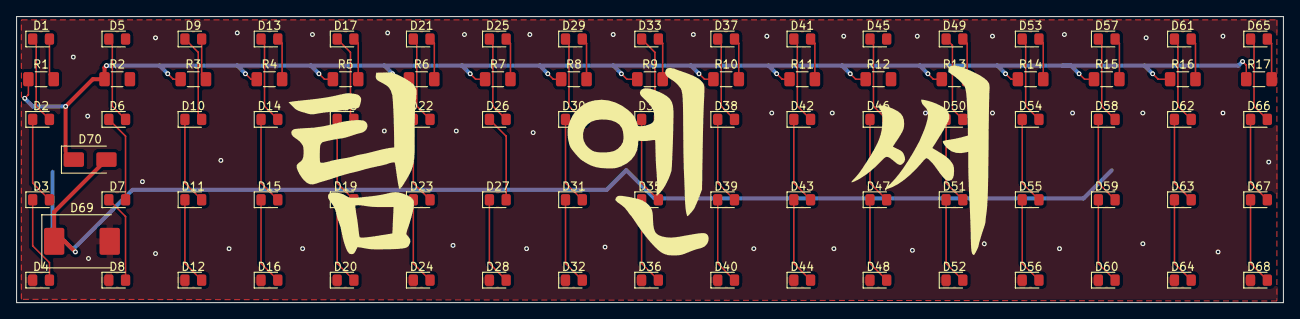
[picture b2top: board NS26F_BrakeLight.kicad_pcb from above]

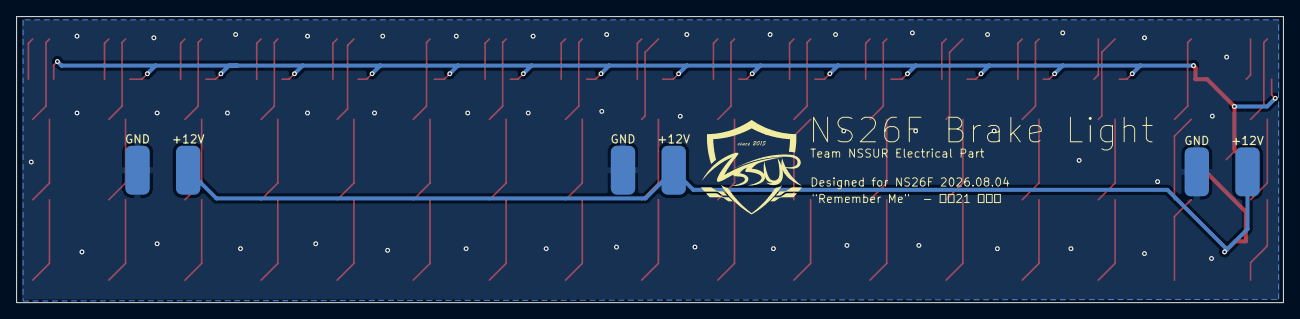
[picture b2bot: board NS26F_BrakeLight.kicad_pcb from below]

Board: 2 copper layers, 155.0 x 35.0 mm, 93 parts (6 on the bottom side), 71 nets.

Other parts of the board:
+12V, +12V#2, +12V#3: SolderWirePad_1x01_SMD_3x6mm
GND: SolderWirePad_1x01_SMD_3x6mm
GND#2, GND#3: SolderWirePad_1x01_SMD_3x6mm

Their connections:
+12V: +12V.1, +12V#2.1, +12V#3.1; also elsewhere on the board
GND: GND.1, GND#2.1, GND#3.1; also elsewhere on the board

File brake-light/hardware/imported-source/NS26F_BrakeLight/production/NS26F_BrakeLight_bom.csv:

Designator,Footprint,Quantity,Value,LCSC Part #
"D1, D10, D11, D12, D13, D14, D15, D16, D17, D18, D19, D2, D20, D21, D22, D23, D24, D25, D26, D27, D28, D29, D3, D30, D31, D32, D33, D34, D35, D36, D37, D38, D39, D4, D40, D41, D42, D43, D44, D45, D46, D47, D48, D49, D5, D50, D51, D52, D53, D54, D55, D56, D57, D58, D59, D6, D60, D61, D62, D63, D64, D65, D66, D67, D68, D7, D8, D9",0805,68,LED,
D69,D_SMC,1,D_TVS,
D70,D_SMA,1,SS34,
"R1, R10, R11, R12, R13, R14, R15, R16, R17, R2, R3, R4, R5, R6, R7, R8, R9",1206,17,330,

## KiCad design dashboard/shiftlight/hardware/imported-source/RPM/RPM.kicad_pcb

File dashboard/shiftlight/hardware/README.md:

# Shift Light Hardware

KiCad 프로젝트 위치: `imported-source/RPM/`

- `RPM.kicad_sch`: 회로도
- `RPM.kicad_pcb`: PCB
- `RPM.kicad_pro`: 프로젝트 설정
- `RPM-*.gbr`, `RPM-job.gbrjob`: Gerber
- `production/*_bom.csv`: BOM
- `production/*_positions.csv`: 실장 좌표
- `production/*.zip`: 생산 파일

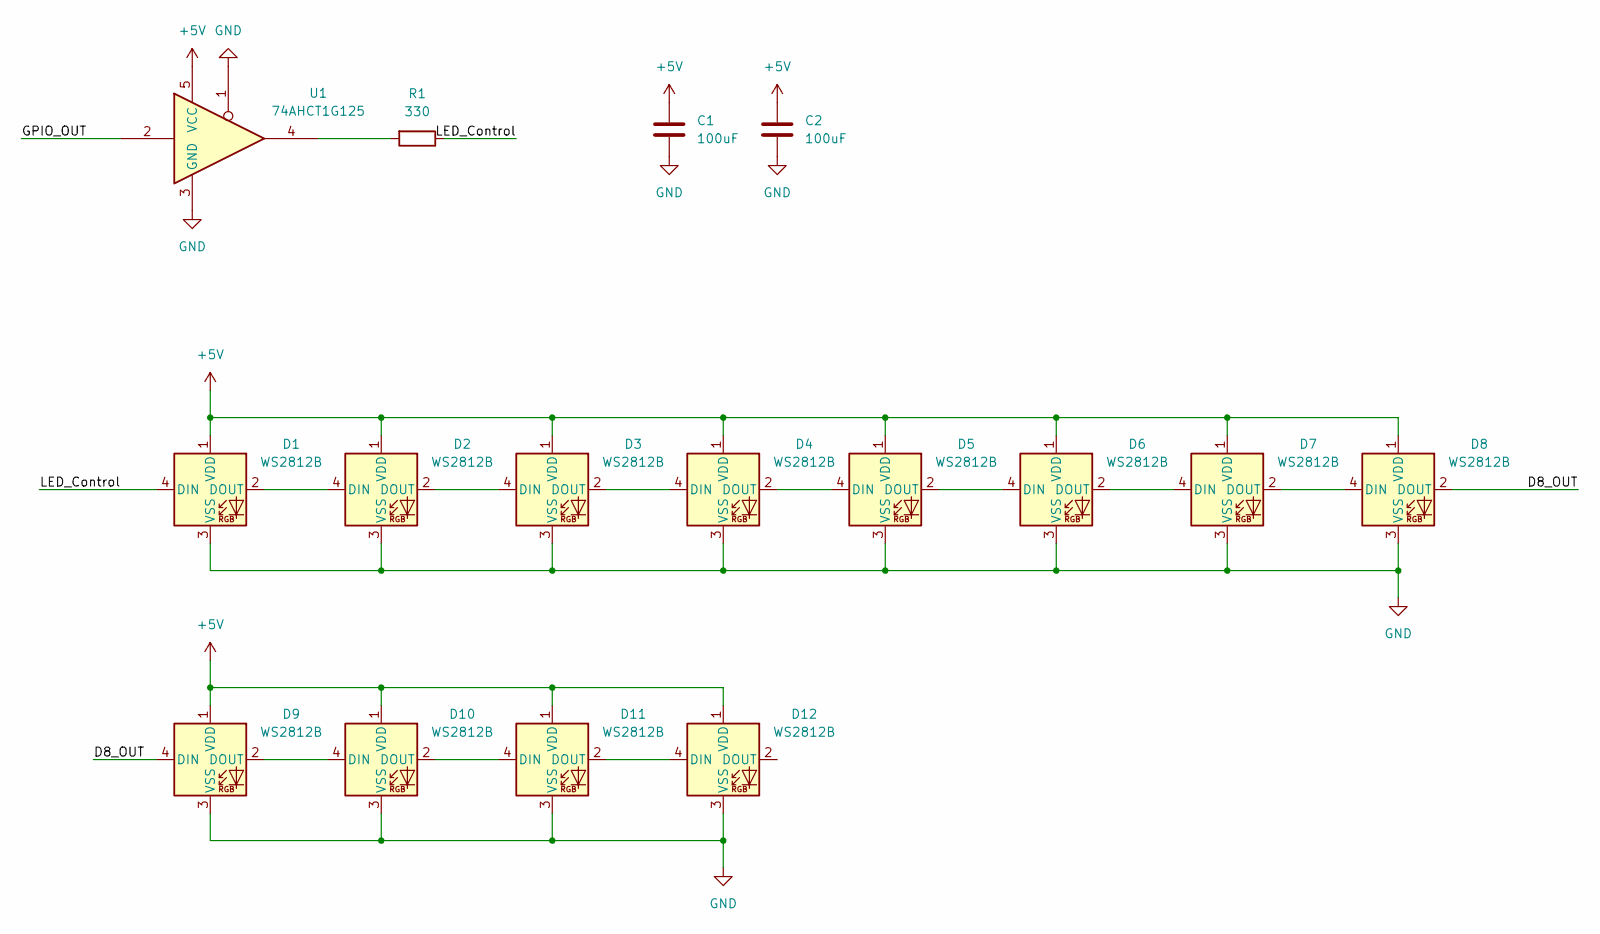
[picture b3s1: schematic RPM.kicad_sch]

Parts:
C1, C2: 100uF; C_1206_3216Metric_Pad1.33x1.80mm_HandSolder
D1, D2, D3, D4, D5, D6, D7, D8, D9, D10, D11, D12: WS2812B; LED_WS2812B_PLCC4_5.0x5.0mm_P3.2mm
R1: 330; R_0805_2012Metric_Pad1.20x1.40mm_HandSolder
U1: 74AHCT1G125; SOT-23-5_HandSoldering

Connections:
+5V: C1.1, C2.1, D1.1 (VDD), D2.1 (VDD), D3.1 (VDD), D4.1 (VDD), D5.1 (VDD), D6.1 (VDD), D7.1 (VDD), D8.1 (VDD), D9.1 (VDD), D10.1 (VDD), D11.1 (VDD), D12.1 (VDD), U1.5 (VCC)
/D8_OUT: D8.2 (DOUT), D9.4 (DIN)
/GPIO_OUT: U1.2
/LED_Control: D1.4 (DIN), R1.1
GND: C1.2, C2.2, D1.3 (VSS), D2.3 (VSS), D3.3 (VSS), D4.3 (VSS), D5.3 (VSS), D6.3 (VSS), D7.3 (VSS), D8.3 (VSS), D9.3 (VSS), D10.3 (VSS), D11.3 (VSS), D12.3 (VSS), U1.1, U1.3 (GND)
unnamed: D1.2 (DOUT), D2.4 (DIN)
unnamed: D2.2 (DOUT), D3.4 (DIN)
unnamed: D3.2 (DOUT), D4.4 (DIN)
unnamed: D4.2 (DOUT), D5.4 (DIN)
unnamed: D5.2 (DOUT), D6.4 (DIN)
unnamed: D6.2 (DOUT), D7.4 (DIN)
unnamed: D7.2 (DOUT), D8.4 (DIN)
unnamed: D9.2 (DOUT), D10.4 (DIN)
unnamed: D10.2 (DOUT), D11.4 (DIN)
unnamed: D11.2 (DOUT), D12.4 (DIN)
unnamed: R1.2, U1.4

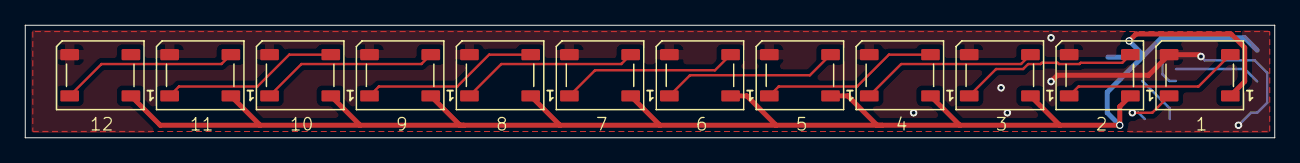
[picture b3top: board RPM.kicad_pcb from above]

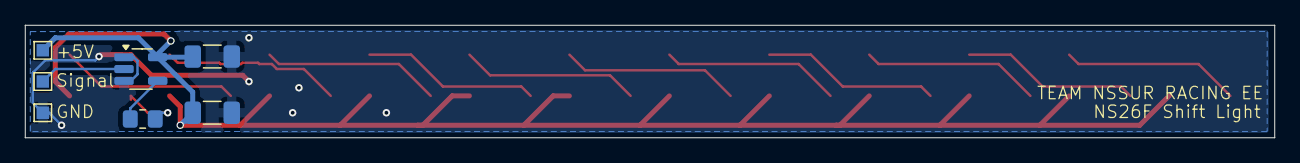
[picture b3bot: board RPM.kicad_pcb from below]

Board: 2 copper layers, 100.0 x 9.0 mm, 16 parts (4 on the bottom side), 15 nets.

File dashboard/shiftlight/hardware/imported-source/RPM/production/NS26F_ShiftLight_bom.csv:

Designator,Footprint,Quantity,Value,LCSC Part #
"C1, C2",1206,2,100uF,
"D1, D10, D11, D12, D2, D3, D4, D5, D6, D7, D8, D9",LED_WS2812B_PLCC4_5.0x5.0mm_P3.2mm,12,WS2812B,
R1,0805,1,330,
U1,SOT-23-5_HandSoldering,1,74AHCT1G125,

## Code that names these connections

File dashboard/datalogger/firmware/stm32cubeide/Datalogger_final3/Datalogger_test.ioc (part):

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Mcu.Name=STM32F405RGTx
Mcu.Package=LQFP64
Mcu.UserName=STM32F405RGTx
PA0-WKUP.Mode=Asynchronous
PA0-WKUP.Signal=UART4_TX
PA1.Mode=Asynchronous
PA1.Signal=UART4_RX
PA10.Mode=Asynchronous
PA10.Signal=USART1_RX
PA11.Mode=Device_Only
PA11.Signal=USB_OTG_FS_DM
PA12.Mode=Device_Only
PA12.Signal=USB_OTG_FS_DP
PA13.Mode=Serial_Wire
PA13.Signal=SYS_JTMS-SWDIO
PA14.Mode=Serial_Wire
PA14.Signal=SYS_JTCK-SWCLK
PA15.Signal=S_TIM2_CH1_ETR
PA2.Mode=Asynchronous
PA2.Signal=USART2_TX
PA3.Mode=Asynchronous
PA3.Signal=USART2_RX
PA8.Signal=S_TIM1_CH1
PA9.Mode=Asynchronous
PA9.Signal=USART1_TX
PC7.Mode=Asynchronous
PC7.Signal=USART6_RX
PB0.GPIOParameters=GPIO_Label
PB0.GPIO_Label=USER_LED_0
PB0.Signal=GPIO_Output
PB1.GPIOParameters=GPIO_Label
PB1.GPIO_Label=USER_LED_1
PB1.Signal=GPIO_Output
PB10.Signal=S_TIM2_CH3
PB12.GPIOParameters=GPIO_Label
PB12.GPIO_Label=VBUS_Detection
PB12.Signal=GPIO_Input
PB3.Signal=S_TIM2_CH2
PB8.Mode=CAN_Activate
PB8.Signal=CAN1_RX
PB9.Mode=CAN_Activate
PB9.Signal=CAN1_TX
PC0.Signal=ADCx_IN10
PC1.Signal=ADCx_IN11
PC10.Mode=SD_4_bits_Wide_bus
PC10.Signal=SDIO_D2
PC11.Mode=SD_4_bits_Wide_bus
PC11.Signal=SDIO_D3
PC12.Mode=SD_4_bits_Wide_bus
PC12.Signal=SDIO_CK
PC13-ANTI_TAMP.GPIOParameters=GPIO_Label
PC13-ANTI_TAMP.GPIO_Label=SD_Detect
PC13-ANTI_TAMP.Signal=GPIO_Input
PC2.Signal=ADCx_IN12
PC3.Signal=ADCx_IN13
PC4.Signal=ADCx_IN14
PC5.Signal=ADCx_IN15
PC6.Signal=S_TIM8_CH1
PC8.Mode=SD_4_bits_Wide_bus
PC8.Signal=SDIO_D0
PC9.Mode=SD_4_bits_Wide_bus
PC9.Signal=SDIO_D1
PD2.Mode=SD_4_bits_Wide_bus
PD2.Signal=SDIO_CMD
PH0-OSC_IN.Mode=HSE-External-Oscillator
PH0-OSC_IN.Signal=RCC_OSC_IN
PH1-OSC_OUT.Mode=HSE-External-Oscillator
PH1-OSC_OUT.Signal=RCC_OSC_OUT
RCC.HSE_VALUE=8000000
RCC.SYSCLKFreq_VALUE=72000000
RCC.SYSCLKSource=RCC_SYSCLKSOURCE_PLLCLK
board=custom
